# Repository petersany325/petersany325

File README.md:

# ریپوی پروژه‌های جدا — بدون Windex / WinFOF / SASDEX

این ریپو **شامل نرم‌افزار Windex، WinFOF، SASDEX یا ابزار فکتوری هارد نیست.**

## پروژه‌های داخل ریپو

### ۱) سایت مؤسسه حقوقی آریان (`aryan-law-*`)
- `aryan-law-html/` — طرح HTML اولیه
- `aryan-law-php/` — نسخه PHP ساده بدون دیتابیس
- `aryan-law-laravel/` — لاراول ۱۳ با نصب‌کننده وب + پنل ادمین
- `aryan-law-php-host.zip` — پکیج PHP برای هاست
- `aryan-law-laravel-cpanel-install.zip` — پکیج لاراول برای cPanel (همراه vendor)

نصب لاراول روی هاست: [`aryan-law-laravel/INSTALL-CPANEL.md`](aryan-law-laravel/INSTALL-CPANEL.md)

1. ZIP لاراول را آپلود و Extract کنید  
2. Document Root را روی `public` بگذارید  
3. PHP **8.3** با mbstring/fileinfo/pdo_mysql  
4. بروید به `/install` و مشخصات دیتابیس را بزنید  
5. ایمیل و رمز ادمین نمایش داده می‌شود → `/admin`

### ۲) ربات تلگرام همگپ (`hamgap-bot*`)
- `hamgap-bot/` — کد ربات
- `hamgap-bot-design/` — دارایی‌های طراحی

### ۳) طراحی برد SATA→USB (`usb-bridge-boards/`)
- `usb-bridge-boards/jms578-sata-usb/` — شماتیک، BOM، مشخصات PCB استیک JMicron JMS578
- فقط طراحی سخت‌افزار/مستندات؛ نرم‌افزار فکتوری هارد اینجا نیست

## نام‌هایی که عمداً اینجا نیستند
- **Windex / Windex WD** — حذف شده از این ریپو  
- **WinFOF** — اینجا نیست  
- **SASDEX** — اینجا نیست

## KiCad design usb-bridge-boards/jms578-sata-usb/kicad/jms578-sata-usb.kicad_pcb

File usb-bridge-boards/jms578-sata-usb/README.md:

# JMS578 — استیک SATA → USB 3.0

برد باریک شبیه «آداپتر فکتوری»: USB-A نر، **کلید ON/OFF**، جک DC کمکی، کانکتور SATA دیتا + تغذیه — **PCB دو لایه**.

## مشخصات

| آیتم | مقدار |
|------|--------|
| پل | JMicron **JMS578** (QFN-48) |
| سرعت | USB 3.1 Gen1 / USB 3.0 — تا ~۵ Gbps (~۴۰۰–۴۵۰ MB/s واقعی) |
| خروجی | SATA 6 Gb/s + برق ۵V (۲٫۵ اینچ) |
| ورودی | USB-A نر؛ جک DC ۵V اختیاری |
| کلید | **ON / OFF** راکر روی مسیر ۵V (قطع کامل برد و دیسک) |
| کاربرد | هارد/SSD ۲٫۵"، mSATA (با تبدیل)، کار فکتوری/开卡 (مثل SM2244LT) |
| لایه‌ها | **۲ لایه** — Top سیگنال، Bottom GND یکپارچه |
| ابعاد هدف | حدود **۸۵ × ۲۲ mm** (استیک) |

## فایل‌های طراحی

| فایل | محتوا |
|------|--------|
| [`FAB.md`](FAB.md) | تفاوت `.PcbDoc` / Gerber و راهنمای چاپ |
| [`jms578-sata-usb-gerbers.zip`](jms578-sata-usb-gerbers.zip) | **فایل چاپ** (Gerber+Drill) |
| [`kicad/jms578-sata-usb.kicad_pcb`](kicad/jms578-sata-usb.kicad_pcb) | پروژه KiCad دو لایه |
| [`pcb-preview.svg`](pcb-preview.svg) | پیش‌نمایش برد |
| [`SCHEMATIC.md`](SCHEMATIC.md) | شماتیک بلوکی + اتصالات پایه |
| [`bom.csv`](bom.csv) | لیست قطعات سفارش |
| [`pcb-spec.md`](pcb-spec.md) | مکانیک، استک‌آپ، قوانین مسیردهی |
| [`floorplan.svg`](floorplan.svg) / [`floorplan.png`](floorplan.png) | جانمایی فیزیکی |
| [`schematic-block.svg`](schematic-block.svg) / [`schematic-block.png`](schematic-block.png) | دیاگرام بلوکی |
| [`nets.csv`](nets.csv) | نت‌لیست فشرده |
| [`pinout-jms578.md`](pinout-jms578.md) | پایه به پایه JMS578 |

> `.PcbDoc` فرمت Altium است و اینجا تولید نمی‌شود. برای چاپ از **Gerber ZIP** استفاده کن — جزئیات در `FAB.md`.

## جریان تغذیه

```
USB VBUS (5V) ──┐
                ├─(دیود OR)──► SW1 ON/OFF ──┬──► JMS578 5V
DC Jack 5V ─────┘                           └──► SATA 5V (2.5")
                                                      │
                                         داخل JMS578: LDO 3.3V + Buck 1.2V
```

- **OFF**: برق برد و دیسک قطع — امن برای تعویض دیسک / شورت ROM.
- **ON**: تغذیه فعال.

برای هارد **۳٫۵ اینچ** این بورد کافی نیست؛ ۱۲V جدا لازم است.

## ساخت

1. قطعات `bom.csv` را سفارش دهید (چیپ و Flash از AliExpress/LCSC).
2. PCB را طبق `pcb-spec.md` به JLCPCB بفرستید (**۲ لایه**).
3. فریمور را روی SPI Flash بریزید (۵۱۲ Kbit).
4. تست: دیسک وصل → کلید **ON** → در Device Manager باید Mass Storage دیده شود.

## فریمور

- ظرفیت Flash: ترجیحاً **۵۱۲ Kbit (۶۴ KB)** SPI NOR.
- بدون دیسک روی SATA بعضی نسخه‌ها بالا نمی‌آیند؛ برای فلش معمولاً دیسک وصل باشد.
- رفرنس عمومی جامعه: فریمورهای JMS578 منتشرشده در usbdev.ru / OSHWHUB (مثلاً Hardkernel v173).

## محدودیت‌ها

- فقط **۲٫۵ اینچ / ۵V** (نه ۳٫۵ اینچ مگر نسخه با آداپتور ۱۲V).
- روی لینوکس گاهی UAS quirk لازم است (`152d:0578`).
- Auto-spindown فریمور OEM ممکن است فعال باشد؛ در صورت نیاز فریمور را عوض کنید.

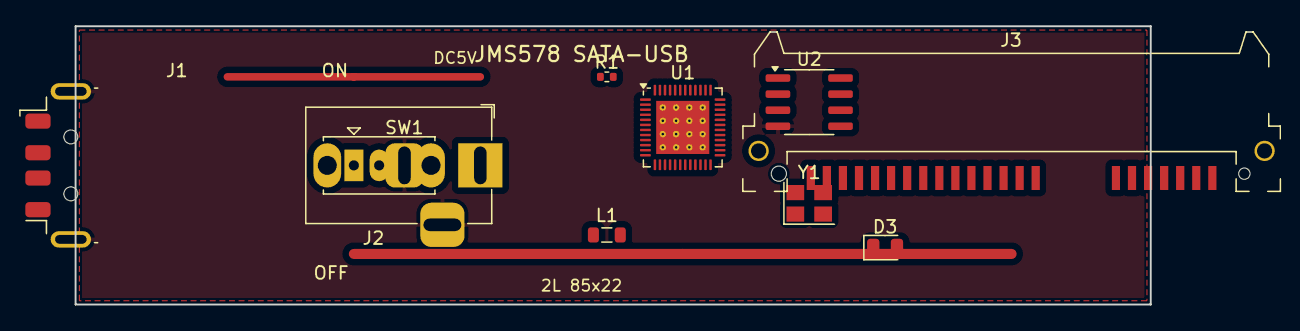
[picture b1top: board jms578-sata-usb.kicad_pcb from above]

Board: 2 copper layers, 85.0 x 22.0 mm, 10 parts (0 on the bottom side), 2 nets.

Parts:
D3: ACT; LED_0805_2012Metric
J1: USB3-A; USB_A_Molex_48037-2200_Horizontal
J2: DC5V; BarrelJack_Horizontal
J3: SATA; SATA_Amphenol_10029364-001LF_Horizontal
L1: 4.7uH; L_0805_2012Metric
R1: 12k; R_0402_1005Metric
SW1: ON/OFF; SW_Slide_SPDT_Straight_CK_OS102011MS2Q
U1: JMS578; QFN-48-1EP_6x6mm_P0.4mm_EP4.2x4.2mm_ThermalVias
U2: Flash512K; SOIC-8_3.9x4.9mm_P1.27mm
Y1: 30MHz; Crystal_SMD_3225-4Pin_3.2x2.5mm

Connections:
GND: J1.4, J1.5, J2.2, J2.3, U1.49, U2.4
V5_OR: SW1.1, SW1.3
